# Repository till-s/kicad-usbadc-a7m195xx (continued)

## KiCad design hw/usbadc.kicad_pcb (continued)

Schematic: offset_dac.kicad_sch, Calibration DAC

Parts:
C98, C105, C107, C108, C109, C147, C148: 100n; C_0603_1608Metric; Part CL10B104KB8NFN
C99, C106, C112, C113: 1u; C_0805_2012Metric; Part CGA4J2X7R1C105K125AA
Q1, Q3: SSM6N35AFE; SOT-563-adjusted; Part SSM6N35AFE
R25, R35, R90, R91, R92, R93: 80k6; R_0603_1608Metric; Part RMCF0603FT80K6
R48, R49: 100k; R_0603_1608Metric; Part RMCF0603FT100K
R61, R62, R71, R79, R87, R89: 18k; R_0603_1608Metric; Part RMCF0603FT18K0
R80, R81, R82, R85: 1k; R_0603_1608Metric; Part RMCF0603FT1K00
R86, R88: 59k0; R_0603_1608Metric; Part RMCF0603FT59K0
R94, R95: 1; R_0603_1608Metric; Part RMCF0603FT1R00
U22: TSV992A; DFN-8-1EP_2x2mm_P0.5mm_EP0.45x1.6mm; Part TSV992IQ2
U23: MCP47CVB12-E_UN; MSOP-10_3x3mm_P0.5mm; Part MCP47CVB12-E/UN

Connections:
+2V5_analog: C105.1, C106.1, C107.2, U22.8 (V+), U23.1 (VDD), U23.2 (A0); also elsewhere on the board
-2V5_analog: C98.1, C99.1, U22.4 (V-); also elsewhere on the board
/Front End/FE_CHA/PGA_INLO: C113.1, R93.1, R95.1; also elsewhere on the board
/Front End/FE_CHB/PGA_INLO: C112.1, R92.1, R94.1; also elsewhere on the board
/Front End/fe_ctl/P0: Q1.2 (G), Q1.5 (G), R48.2; also elsewhere on the board
/Front End/fe_ctl/P1: Q3.2 (G), Q3.5 (G), R49.2; also elsewhere on the board
/I2C_SCL_2V5: U23.9 (SCL); also elsewhere on the board
/I2C_SDA_2V5: U23.10 (SDA); also elsewhere on the board
GND: C98.2, C99.2, C105.2, C106.2, C107.1, C112.2, C113.2, C147.2, C148.2, Q1.1 (S), Q1.4 (S), Q3.1 (S), Q3.4 (S), R25.1, R35.1, R48.1, R49.1, R90.2, R91.2, U23.6 (LATn), U23.7 (VSS), U23.8 (A1); also elsewhere on the board
unnamed: C108.1, R94.2, U22.1
unnamed: C109.1, R95.2, U22.7
unnamed: Q1.6 (D), R80.1
unnamed: Q1.3 (D), R81.1
unnamed: Q3.6 (D), R82.1
unnamed: Q3.3 (D), R85.1
unnamed: R61.2, R80.2, R86.1
unnamed: R62.2, R81.2, R87.1
unnamed: R71.2, R82.2, R88.1
unnamed: R79.2, R85.2, R89.1
unnamed: C148.1, R25.2, R86.2, R90.1, U22.3 (+)
unnamed: C108.2, R87.2, R92.2, U22.2 (-)
unnamed: C147.1, R35.2, R88.2, R91.1, U22.5 (+)
unnamed: C109.2, R89.2, R93.2, U22.6 (-)
unnamed: R79.1, U23.4 (VOUT0)
unnamed: R62.1, U23.5 (VOUT1)
unnamed: R61.1, R71.1, U23.3 (VREF)

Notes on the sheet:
I2C Address 0x61 MCP47CVB02: 8-bit MCP47CVB12: 10-bit MCP47CVB22: 12-bit

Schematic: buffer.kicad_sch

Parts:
C2001, C2002, C2003, C2006, C2008, C2010, C2012, C2014, C2016, C2017: 100n; C_0603_1608Metric; Part CL10B104KB8NFN
C2004: 10p; C_0402_1005Metric
C2005: 10n; C_0805_2012Metric
C2007, C2013, C2015: 2n; C_0603_1608Metric
C2009, C2011: 1u; C_0805_2012Metric; Part CGA4J2X7R1C105K125AA
D2001: NSR0170HT1G; D_SOD-323; Part NSR0170HT1G
J2001: BNC; BNC_Molex_0731713150; Part 0731713150
J2002: RFShield_Front; Leader SMS-255F; Part SMS-255F+C
J2003: RFShield_Back; SMS-202F; Part SMS-202F+C
JP2001: 50Ohm; J_0603_V
K2001: G6L-1F; Part G6L-1F
R2001, R2003, R2008: 1M; R_0603_1608Metric
R2002: 1k; R_0603_1608Metric
R2004: 1M; R_0402_1005Metric
R2005: 100k/100p; RC_0603_1608Metric
R2006, R2007: 909k/11p; RC_0603_1608Metric
U2001: TS5A63157DCK; SOT-363_SC-70-6_small_cyd
U2002: AQY280S; SOP-4_3.8x4.1mm_P2.54mm
U2003: AD8370; TSSOP-16-1EP_4.4x5mm_P0.65mm_EP3x3mm_ThermalVias
U2004: OPA859xDSG; WSON-8-1EP_2x2mm_P0.5mm_EP0.9x1.6mm

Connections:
+2V5_analog: C2010.1, C2011.1, C2014.1, C2015.1, C2016.1, C2017.1, U2003.3 (VCCI), U2003.4 (PWUP), U2003.6 (VCCO), U2003.11 (VCCO), U2004.7 (V+), U2004.8 (~PD); also elsewhere on the board
-2V5_analog: C2008.1, C2009.1, C2012.1, C2013.1, C2016.2, C2017.2, R2008.1, U2003.2 (ICOM), U2003.7 (OCOM), U2003.10 (OCOM), U2003.15 (ICOM), U2003.17 (ICOM), U2004.5 (V-); also elsewhere on the board
/ADC/ADC_CHB_IN_N: U2003.8 (OPHI); also elsewhere on the board
/ADC/ADC_CHB_IN_P: U2003.9 (OPLO); also elsewhere on the board
/Front End/FE_CHA/PGA_CTL_CLK: U2003.13 (CLCK); also elsewhere on the board
/Front End/FE_CHA/PGA_CTL_DATA: U2003.14 (DATA); also elsewhere on the board
/Front End/FE_CHB/FE_CTL_AC: R2002.2; also elsewhere on the board
/Front End/FE_CHB/FE_CTL_ATT: R2001.2, R2003.2; also elsewhere on the board
/Front End/FE_CHB/FE_CTL_TERM: D2001.1 (K), K2001.5; also elsewhere on the board
/Front End/FE_CHB/PGA_CTL_LATCH: U2003.12 (LTCH); also elsewhere on the board
/Front End/FE_CHB/PGA_INLO: C2003.1, U2003.16 (INLO); also elsewhere on the board
GND: C2001.2, C2002.1, C2003.2, C2006.1, C2007.2, C2008.2, C2009.2, C2010.2, C2011.2, C2012.2, C2013.2, C2014.2, C2015.2, D2001.2 (A), J2001.2 (Ext), J2002.1 (Shield), J2003.1 (Shield), K2001.2, K2001.8, R2003.1, U2001.2 (GND), U2001.3 (NC), U2002.2, U2004.4 (+); also elsewhere on the board
unnamed: C2005.2, J2001.1 (In), JP2001.1 (A), U2002.4
unnamed: C2005.1, JP2001.3 (B), R2006.2, U2002.3
unnamed: JP2001.2 (C), K2001.4
unnamed: R2002.1, U2002.1
unnamed: R2005.2, R2006.1, R2007.2
unnamed: R2005.1, U2001.4 (COM)
unnamed: C2001.1, R2001.1, U2001.6 (IN)
unnamed: C2004.1, R2004.2, R2007.1, U2001.1 (NO), U2004.3 (-)
unnamed: U2003.1 (INHI), U2004.6
unnamed: C2007.1, U2003.5 (VOCM)
unnamed: C2006.2, R2008.2, U2004.9 (EP)
unnamed: C2004.2, R2004.1, U2004.1 (FB)
Vpp_analog: C2002.2, U2001.5 (V+); also elsewhere on the board

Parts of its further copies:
C1001, C1002, C1003, C1006, C1008, C1010, C1012, C1014, C1016, C1017: 100n; C_0603_1608Metric; Part CL10B104KB8NFN
C1004: 10p; C_0402_1005Metric
C1005: 10n; C_0805_2012Metric
C1007, C1013, C1015: 2n; C_0603_1608Metric
C1009, C1011: 1u; C_0805_2012Metric; Part CGA4J2X7R1C105K125AA
D1001: NSR0170HT1G; D_SOD-323; Part NSR0170HT1G
J1001: BNC; BNC_Molex_0731713150; Part 0731713150
J1002: RFShield_Front; Leader SMS-255F; Part SMS-255F+C
J1003: RFShield_Back; SMS-202F; Part SMS-202F+C
JP1001: 50Ohm; J_0603_V
K1001: G6L-1F; Part G6L-1F
R1001, R1003, R1008: 1M; R_0603_1608Metric
R1002: 1k; R_0603_1608Metric
R1004: 1M; R_0402_1005Metric
R1005: 100k/100p; RC_0603_1608Metric
R1006, R1007: 909k/11p; RC_0603_1608Metric
U1001: TS5A63157DCK; SOT-363_SC-70-6_small_cyd
U1002: AQY280S; SOP-4_3.8x4.1mm_P2.54mm
U1003: AD8370; TSSOP-16-1EP_4.4x5mm_P0.65mm_EP3x3mm_ThermalVias
U1004: OPA859xDSG; WSON-8-1EP_2x2mm_P0.5mm_EP0.9x1.6mm

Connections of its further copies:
+2V5_analog: C1010.1, C1011.1, C1014.1, C1015.1, C1016.1, C1017.1, U1003.3 (VCCI), U1003.4 (PWUP), U1003.6 (VCCO), U1003.11 (VCCO), U1004.7 (V+), U1004.8 (~PD); also elsewhere on the board
-2V5_analog: C1008.1, C1009.1, C1012.1, C1013.1, C1016.2, C1017.2, R1008.1, U1003.2 (ICOM), U1003.7 (OCOM), U1003.10 (OCOM), U1003.15 (ICOM), U1003.17 (ICOM), U1004.5 (V-); also elsewhere on the board
/ADC/ADC_CHA_IN_N: U1003.8 (OPHI); also elsewhere on the board
/ADC/ADC_CHA_IN_P: U1003.9 (OPLO); also elsewhere on the board
/Front End/FE_CHA/FE_CTL_AC: R1002.2; also elsewhere on the board
/Front End/FE_CHA/FE_CTL_ATT: R1001.2, R1003.2; also elsewhere on the board
/Front End/FE_CHA/FE_CTL_TERM: D1001.1 (K), K1001.5; also elsewhere on the board
/Front End/FE_CHA/PGA_CTL_CLK: U1003.13 (CLCK); also elsewhere on the board
/Front End/FE_CHA/PGA_CTL_DATA: U1003.14 (DATA); also elsewhere on the board
/Front End/FE_CHA/PGA_CTL_LATCH: U1003.12 (LTCH); also elsewhere on the board
/Front End/FE_CHA/PGA_INLO: C1003.1, U1003.16 (INLO); also elsewhere on the board
GND: C1001.2, C1002.1, C1003.2, C1006.1, C1007.2, C1008.2, C1009.2, C1010.2, C1011.2, C1012.2, C1013.2, C1014.2, C1015.2, D1001.2 (A), J1001.2 (Ext), J1002.1 (Shield), J1003.1 (Shield), K1001.2, K1001.8, R1003.1, U1001.2 (GND), U1001.3 (NC), U1002.2, U1004.4 (+); also elsewhere on the board
unnamed: C1005.2, J1001.1 (In), JP1001.1 (A), U1002.4
unnamed: C1005.1, JP1001.3 (B), R1006.2, U1002.3
unnamed: JP1001.2 (C), K1001.4
unnamed: R1002.1, U1002.1
unnamed: R1005.2, R1006.1, R1007.2
unnamed: R1005.1, U1001.4 (COM)
unnamed: C1001.1, R1001.1, U1001.6 (IN)
unnamed: C1004.1, R1004.2, R1007.1, U1001.1 (NO), U1004.3 (-)
unnamed: U1003.1 (INHI), U1004.6
unnamed: C1007.1, U1003.5 (VOCM)
unnamed: C1006.2, R1008.2, U1004.9 (EP)
unnamed: C1004.2, R1004.1, U1004.1 (FB)
Vpp_analog: C1002.2, U1001.5 (V+); also elsewhere on the board

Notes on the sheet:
Ideally: 101k//99p but 99p is not available
Populate 1-2 or 2-3 with 50Ohm termination resistor depending on whether you like the termination to be AC- or DC-coupled.

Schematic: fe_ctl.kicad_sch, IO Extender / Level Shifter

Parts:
C9, C140: 100n; C_0603_1608Metric; Part CL10B104KB8NFN
R60: 10k; R_0603_1608Metric; Part RMCF0603FT10K0
U21: TCA6408A; QFN-16-1EP_3x3mm_P0.5mm_EP1.45x1.45mm_ThermalVias; Part TCA6408ARGTR

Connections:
+3V3: C140.1, R60.2, U21.15 (VCCi); also elsewhere on the board
+4V: C9.1, U21.14 (VCCp); also elsewhere on the board
/Front End/FE_CHA/FE_CTL_AC: U21.8 (P5); also elsewhere on the board
/Front End/FE_CHA/FE_CTL_ATT: U21.7 (P4); also elsewhere on the board
/Front End/FE_CHB/FE_CTL_AC: U21.5 (P3); also elsewhere on the board
/Front End/FE_CHB/FE_CTL_ATT: U21.4 (P2); also elsewhere on the board
/Front End/fe_ctl/P0: U21.2 (P0); also elsewhere on the board
/Front End/fe_ctl/P1: U21.3 (P1); also elsewhere on the board
/Front End/fe_ctl/P6: U21.9 (P6); also elsewhere on the board
/Front End/fe_ctl/P7: U21.10 (P7); also elsewhere on the board
GND: C9.2, C140.2, U21.6 (GND), U21.16 (ADDR); also elsewhere on the board
I2C_SCL_3V3: U21.12 (SCL); also elsewhere on the board
I2C_SDA_3V3: U21.13 (SDA); also elsewhere on the board
unnamed: R60.1, U21.1 (RESETb)

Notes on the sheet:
NOTES: I2C Address 0x40 ADDR: VCCp levels RESETb: VCCi levels PAD: seems unconnected

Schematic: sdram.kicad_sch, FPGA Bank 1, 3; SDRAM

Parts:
C37, C39, C50, C51, C52, C53, C54, C55, C84, C86, C92, C93, C94: 100n; C_0603_1608Metric; Part CL10B104KB8NFN
C38, C72: 4u7; C_0805_2012Metric; Part 2012X5R1C475K125AC
FB4: 600Ohm@100MHz; L_0603_1608Metric; Part MI0603J601R-10
R83, R84, R100, R101, R102, R121: 10k; R_0603_1608Metric; Part RMCF0603FT10K0
R122: 10k; R_0603_1608Metric; Part RMCF0603FT10K0; not fitted
U15: T20Q144xx; LQFP-144_20x20mm_P0.5mm; Part T20Q144C4
U17: NDS36PT5-16ET; TSOP-II-54_22.2x10.16mm_P0.8mm; Part NDS36PT5-16ET

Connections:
+3V3: C37.1, C38.1, C39.1, C50.1, C51.1, C84.1, C86.1, C92.1, C93.1, C94.1, FB4.2, R83.1, R84.1, R100.1, R101.1, R102.1, R121.1, U15.12 (VCCIO1C_1D), U15.21 (VCCIO1B), U15.88 (VCCIO3E), U15.91 (VCCIO3D), U15.95 (VCCIO3B_3C), U15.143 (VCCIO1E), U17.1 (VDD), U17.14 (VDD), U17.27 (VDD); also elsewhere on the board
/FPGA Trion/sdram/A0: U15.144 (GPIOL_64), U17.23 (A0)
/FPGA Trion/sdram/A1: U15.138 (GPIOL_69_CBSEL1), U17.24 (A1)
/FPGA Trion/sdram/A2: U15.140 (GPIOL_67_CDI13), U17.25 (A2)
/FPGA Trion/sdram/A3: U15.141 (GPIOL_65), U17.26 (A3)
/FPGA Trion/sdram/A6: U15.106 (GPIOR_94_CDI27), U17.31 (A6)
/FPGA Trion/sdram/A7: U15.105 (GPIOR_95_CDI26), U17.32 (A7)
/FPGA Trion/sdram/A8: U15.103 (GPIOR_104_CDI25), U17.33 (A8)
/FPGA Trion/sdram/A9: U15.102 (GPIOR_105_CDI24), U17.34 (A9)
/FPGA Trion/sdram/A10: U15.142 (GPIOL_66_CDI12), U17.22 (A10)
/FPGA Trion/sdram/BA0: U15.4 (GPIOL_54_CDI11), U17.20 (BA0)
/FPGA Trion/sdram/BA1: U15.3 (GPIOL_53_CDI10), U17.21 (BA1)
/FPGA Trion/sdram/CASb: U15.8 (GPIOL_40_CDI8), U17.17 (~CAS)
/FPGA Trion/sdram/CLK: U15.98 (GPIOR_117_CTRL14), U17.38 (CLK)
/FPGA Trion/sdram/CSb: R83.2, U15.6 (GPIOL_46), U17.19 (~CS)
/FPGA Trion/sdram/DQ1: U15.20 (GPIOL_12_CDI2), U17.4 (DQ1)
/FPGA Trion/sdram/DQ2: U15.19 (GPIOL_13_CDI3), U17.5 (DQ2)
/FPGA Trion/sdram/DQ3: U15.18 (GPIOL_20_CTRL0_CDI4), U17.7 (DQ3)
/FPGA Trion/sdram/DQ4: U15.17 (GPIOL_21_CTRL1_CDI5), U17.8 (DQ4)
/FPGA Trion/sdram/DQ5: U15.16 (GPIOL_22_CTRL2), U17.10 (DQ5)
/FPGA Trion/sdram/DQ6: U15.15 (GPIOL_24_CLK0), U17.11 (DQ6)
/FPGA Trion/sdram/DQ7: U15.14 (GPIOL_25_CLK1), U17.13 (DQ7)
/FPGA Trion/sdram/DQ8: U15.100 (GPIOR_113_CDI22), U17.42 (DQ8)
/FPGA Trion/sdram/DQ9: U15.99 (GPIOR_116_CTRL15), U17.44 (DQ9)
/FPGA Trion/sdram/DQ10: U15.97 (GPIOR_122_CLK13_CDI21), U17.45 (DQ10)
/FPGA Trion/sdram/DQ11: U15.87 (GPIOR_132_CDI19), U17.47 (DQ11)
/FPGA Trion/sdram/DQ12: U15.86 (GPIOR_133_CDI18), U17.48 (DQ12)
/FPGA Trion/sdram/DQ13: U15.81 (GPIOR_139), U17.50 (DQ13)
/FPGA Trion/sdram/DQ14: U15.77 (GPIOR_154), U17.51 (DQ14)
/FPGA Trion/sdram/DQ15: R84.2, U15.74 (GPIOR_158_TEST_N), U17.53 (DQ15)
/FPGA Trion/sdram/DQMH: U15.101 (GPIOR_112_CDI23), U17.39 (DQMH)
/FPGA Trion/sdram/DQML: U15.11 (GPIOL_31_CLK7_CDI6), U17.15 (DQML)
/FPGA Trion/sdram/RASb: U15.7 (GPIOL_41_CDI9), U17.18 (~RAS)
/FPGA Trion/sdram/WEb: U15.10 (GPIOL_32_CTRL4_CDI7), U17.16 (~WE)
ADC_D0: U15.93 (GPIOR_123_CLK12_CDI20); also elsewhere on the board
ADC_D1: U15.92 (GPIOR_125_CLK10); also elsewhere on the board
ADC_D2: U15.90 (GPIOR_128_CTRL11); also elsewhere on the board
ADC_D3: U15.89 (GPIOR_129_CTRL10); also elsewhere on the board
ADC_D4: U15.84 (GPIOR_135_CDI17); also elsewhere on the board
ADC_D5: U15.83 (GPIOR_136_CDI16); also elsewhere on the board
ADC_D6: U15.82 (GPIOR_138); also elsewhere on the board
ADC_D7: R102.2, U15.80 (GPIOR_149_CBUS2); also elsewhere on the board
ADC_D8: R101.2, U15.79 (GPIOR_150_CBUS1); also elsewhere on the board
ADC_D9: R100.2, U15.78 (GPIOR_151_CBUS0); also elsewhere on the board
ADC_DCLK: U15.75 (GPIOR_157_PLLIN); also elsewhere on the board
ADC_DOR: U15.76 (GPIOR_155); also elsewhere on the board
ADC_SHDN: R121.2, R122.1; also elsewhere on the board
GND: C37.2, C38.2, C39.2, C50.2, C51.2, C52.2, C53.2, C54.2, C55.2, C72.2, C84.2, C86.2, C92.2, C93.2, C94.2, R122.2, U17.6 (VSSQ), U17.12 (VSSQ), U17.28 (VSS), U17.41 (VSS), U17.46 (VSSQ), U17.52 (VSSQ), U17.54 (VSS); also elsewhere on the board
I2C_SCL_3V3: U15.134 (GPIOL_73_EXTFB1_CDI15); also elsewhere on the board
unnamed: C52.1, C53.1, C54.1, C55.1, C72.1, FB4.1, U17.3 (VDDQ), U17.9 (VDDQ), U17.43 (VDDQ), U17.49 (VDDQ)
SDRAM_A4: U17.29 (A4); also elsewhere on the board
SDRAM_A5: U17.30 (A5); also elsewhere on the board
SDRAM_A11: U17.35 (A11); also elsewhere on the board
SDRAM_A12: U17.36 (A12); also elsewhere on the board
SDRAM_CKE: U15.139 (GPIOL_68), U17.37 (CKE)
SDRAM_DQ0: U17.2 (DQ0); also elsewhere on the board
ULPI_CLK: U15.132 (GPIOL_74_PLLIN0); also elsewhere on the board
ULPI_DIR: U15.135 (GPIOL_72_EXTFB0_CDI14); also elsewhere on the board
ULPI_NXT: U15.131 (GPIOL_75_PLLIN1); also elsewhere on the board
ULPI_RSTb_CLKSEL: U15.137 (GPIOL_70_CBSEL0); also elsewhere on the board
ULPI_STP: U15.136 (GPIOL_71_NSTATUS); also elsewhere on the board

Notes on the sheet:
Prevent ADC from driving ADC_D7..D9 by pulling up ADC_SHDN. Ensures the CBUS configuration pins are pulled up. Once configured the FPGA can drive ADC_SHDN low to activate.

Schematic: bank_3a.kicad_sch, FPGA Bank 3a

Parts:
C36: 100n; C_0603_1608Metric; Part CL10B104KB8NFN
U15: T20Q144xx; LQFP-144_20x20mm_P0.5mm; Part T20Q144C4

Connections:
+3V3: C36.1, U15.122 (VCCIO3A); also elsewhere on the board
FPGA_CLK: U15.124 (GPIOR_76_PLLIN0); also elsewhere on the board
GND: C36.2; also elsewhere on the board
SDRAM_A4: U15.110 (GPIOR_87_CDI29); also elsewhere on the board
SDRAM_A5: U15.109 (GPIOR_88_CDI28); also elsewhere on the board
SDRAM_A11: U15.112 (GPIOR_86); also elsewhere on the board
SDRAM_A12: U15.111 (GPIOR_85); also elsewhere on the board
ULPI_D0: U15.123 (GPIOR_77_PLLIN1); also elsewhere on the board
ULPI_D1: U15.119 (GPIOR_78_EXTFB0_CDI31); also elsewhere on the board
ULPI_D2: U15.118 (GPIOR_79_EXTFB1_CDI30); also elsewhere on the board
ULPI_D3: U15.117 (GPIOR_80); also elsewhere on the board
ULPI_D4: U15.116 (GPIOR_81_MREFCLK); also elsewhere on the board
ULPI_D5: U15.115 (GPIOR_82); also elsewhere on the board
ULPI_D6: U15.114 (GPIOR_83); also elsewhere on the board
ULPI_D7: U15.113 (GPIOR_84); also elsewhere on the board

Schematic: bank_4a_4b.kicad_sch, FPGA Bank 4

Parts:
C137, C138, C139: 100n; C_0603_1608Metric; Part CL10B104KB8NFN
U15: T20Q144xx; LQFP-144_20x20mm_P0.5mm; Part T20Q144C4

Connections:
+3V3: C137.1, C138.1, C139.1, U15.51 (VCCIO4B), U15.52 (VCCIO4B), U15.62 (VCCIO4A), U15.63 (VCCIO4A); also elsewhere on the board
ADC_CSb: U15.70 (GPIOB_RXP12_EXTFB0); also elsewhere on the board
ADC_SCLK: U15.71 (GPIOB_CLKP0); also elsewhere on the board
ADC_SDIO: U15.72 (GPIOB_CLKN0); also elsewhere on the board
ADC_SHDN: U15.53 (GPIOB_TXP11); also elsewhere on the board
ADC_SYNC: U15.66 (GPIOB_RXP07); also elsewhere on the board
EXP_IO1: U15.40 (GPIOB_TXP02); also elsewhere on the board
EXP_IO2: U15.38 (GPIOB_TXP00); also elsewhere on the board
GND: C137.2, C138.2, C139.2; also elsewhere on the board
GPIO_DAT: U15.42 (GPIOB_TXP04); also elsewhere on the board
GPIO_DIR: U15.43 (GPIOB_TXN04); also elsewhere on the board
I2C_SDA_3V3: U15.54 (GPIOB_TXN11); also elsewhere on the board
LED_CHA_B: U15.55 (GPIOB_RXP00); also elsewhere on the board
LED_CHA_G: U15.59 (GPIOB_RXN02); also elsewhere on the board
LED_CHA_R: U15.60 (GPIOB_RXN03); also elsewhere on the board
LED_CHB_B: U15.56 (GPIOB_RXN00); also elsewhere on the board
LED_CHB_G: U15.61 (GPIOB_RXP03); also elsewhere on the board
LED_CHB_R: U15.58 (GPIOB_RXP02); also elsewhere on the board
LED_FL_B: U15.41 (GPIOB_TXN02); also elsewhere on the board
LED_FL_G: U15.39 (GPIOB_TXN00); also elsewhere on the board
LED_FR_B: U15.47 (GPIOB_TXP09); also elsewhere on the board
LED_FR_G: U15.45 (GPIOB_TXP06); also elsewhere on the board
LED_FR_R: U15.48 (GPIOB_TXN09); also elsewhere on the board
LED_FR_S: U15.46 (GPIOB_TXN06); also elsewhere on the board
PGA_LATCH_CHA: U15.68 (GPIOB_RXN10); also elsewhere on the board
PGA_LATCH_CHB: U15.67 (GPIOB_RXP10); also elsewhere on the board
PGA_SCLK: U15.69 (GPIOB_RXN12_EXTFB0); also elsewhere on the board
PGA_SDAT: U15.65 (GPIOB_RXN07); also elsewhere on the board

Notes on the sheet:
The filename is 'unused' for legacy reasons.
REF_RES is not a GPIO

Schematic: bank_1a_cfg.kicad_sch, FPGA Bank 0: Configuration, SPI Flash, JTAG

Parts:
C95, C96, C118, C120, C122, C124, C125, C126, C127, C128, C129, C130, C131, C132: 100n; C_0603_1608Metric; Part CL10B104KB8NFN
C103, C104, C114, C133, C134, C135: 1u; C_0805_2012Metric; Part CGA4J2X7R1C105K125AA
C117, C136: 10u; C_1206_3216Metric; Part CL31A106KPHNNNE
C119, C121, C123: 4u7; C_0805_2012Metric; Part 2012X5R1C475K125AC
D4: NSR0170HT1G; D_SOD-323; Part NSR0170HT1G
FB6, FB7, FB8: 600Ohm@100MHz; L_0603_1608Metric; Part MI0603J601R-10
J4: T8_JTAG; PinHeader_2x07_P2.00mm_Vertical; Part 2PH2-14-UA
R50, R103, R104, R105, R106, R107, R108, R109, R110, R111, R112, R113, R119, R120: 10k; R_0603_1608Metric; Part RMCF0603FT10K0
R52: 10k; R_0603_1608Metric; Part RMCF0603FT10K0; not fitted
R125: 1k; R_0603_1608Metric; Part RMCF0603FT1K00
SW1: Reconfig; SW_SPST_PTS810_and_PTS841; Part PTS841GKSMTR
U15: T20Q144xx; LQFP-144_20x20mm_P0.5mm; Part T20Q144C4
U24: AT25FF081A-SSHN-B; SOIC-8_3.9x4.9mm_P1.27mm; Part AT25FF081A-SSHN-B
U26: TLV803EA29DBZR; SOT-23; Part TLV803EA29DBZR

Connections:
+1V2: C124.1, C125.1, C126.1, C127.1, C128.1, C129.1, C130.1, C131.1, C132.1, C133.1, C134.1, C135.1, C136.1, FB6.1, FB7.1, FB8.1, U15.13 (VCC), U15.22 (VCC), U15.49 (VCC), U15.57 (VCC), U15.85 (VCC), U15.96 (VCC), U15.125 (VCC), U15.128 (VCC), U15.130 (VCC); also elsewhere on the board
+3V3: C95.1, C96.1, C103.1, C104.1, C114.1, C117.1, R103.1, R104.1, R105.1, R106.1, R107.1, R108.1, R109.1, R110.1, R111.1, R112.1, R113.1, R119.1, U15.23 (VCCIO1A), U24.8 (VCC); also elsewhere on the board
/FPGA Trion/CDON: R111.2, U15.34 (CDONE); also elsewhere on the board
/FPGA Trion/bank_1a_cfg/CRESET_N: J4.3, R110.2, R125.2, U15.35 (CRESET_N)
/PWR_GOOD: D4.1 (K); also elsewhere on the board
GND: C95.2, C96.2, C103.2, C104.2, C114.2, C117.2, C118.2, C119.2, C120.2, C121.2, C122.2, C123.2, C124.2, C125.2, C126.2, C127.2, C128.2, C129.2, C130.2, C131.2, C132.2, C133.2, C134.2, C135.2, C136.2, J4.2, J4.4, J4.6, J4.8, J4.10, J4.12, R50.1, R52.1, SW1.1, SW1.3 (Shield), U15.1 (GND), U15.5 (GND), U15.9 (GND), U15.37 (GND), U15.44 (GND), U15.50 (GND), U15.64 (GND), U15.94 (GND), U15.104 (GND), U15.108 (GND), U15.120 (GND), U15.121 (GND), U15.126 (GND), U15.127 (GND), U15.129 (GND), U15.133 (GND), U24.4 (GND), U26.1 (GND); also elsewhere on the board
LED_FL_R: R104.2, U15.32 (GPIOL_04_CSI); also elsewhere on the board
unnamed: D4.2 (A), R120.2, SW1.2
unnamed: J4.5, R107.2, U15.27 (TDI)
unnamed: J4.7, R108.2, U15.24 (TDO)
unnamed: J4.9, R106.2, U15.26 (TCK)
unnamed: J4.11, R109.2, U15.25 (TMS)
unnamed: J4.13, R105.2
unnamed: R103.2, U15.31 (GPIOL_00_SS_N), U24.1 (~CS)
unnamed: U15.30 (GPIOL_01_CCK), U24.6 (SCK)
unnamed: R50.2, U15.29 (GPIOL_08_CDI0), U24.5 (SI/IO0)
unnamed: R52.2, U15.28 (GPIOL_09_CDI1), U24.2 (SO/IO1)
unnamed: C118.1, C119.1, FB6.2, U15.73 (VCCA_BR)
unnamed: C120.1, C121.1, FB7.2, U15.2 (VCCA_TL)
unnamed: C122.1, C123.1, FB8.2, U15.107 (VCCA_TR)
unnamed: R112.2, U24.7 (~HOLD/IO3)
unnamed: R113.2, U24.3 (~WP/IO2)
unnamed: R125.1, U26.2 (RESET)
unnamed: R119.2, R120.1, U26.3 (V_{DD})
SDRAM_DQ0: U15.33 (GPIOL_05_CSO); also elsewhere on the board

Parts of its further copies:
C1001, C1002, C1008, C1010, C1012, C1014, C1016, C1017: 100n; C_0603_1608Metric; Part CL10B104KB8NFN

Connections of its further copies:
+2V5_analog: C1010.1, C1014.1, C1016.1, C1017.1; also elsewhere on the board
-2V5_analog: C1008.1, C1012.1, C1016.2, C1017.2; also elsewhere on the board
GND: C1001.2, C1002.1, C1008.2, C1010.2, C1012.2, C1014.2; also elsewhere on the board
unnamed 220: C1001.1; also elsewhere on the board
Vpp_analog: C1002.2; also elsewhere on the board

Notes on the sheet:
Note: the RDBZR parts use a different pinout!
JTAG Interface
Board version 3.2 did not populate R50 nor R52; can be used to distinguish board versions. 3.3 populates R50 only.

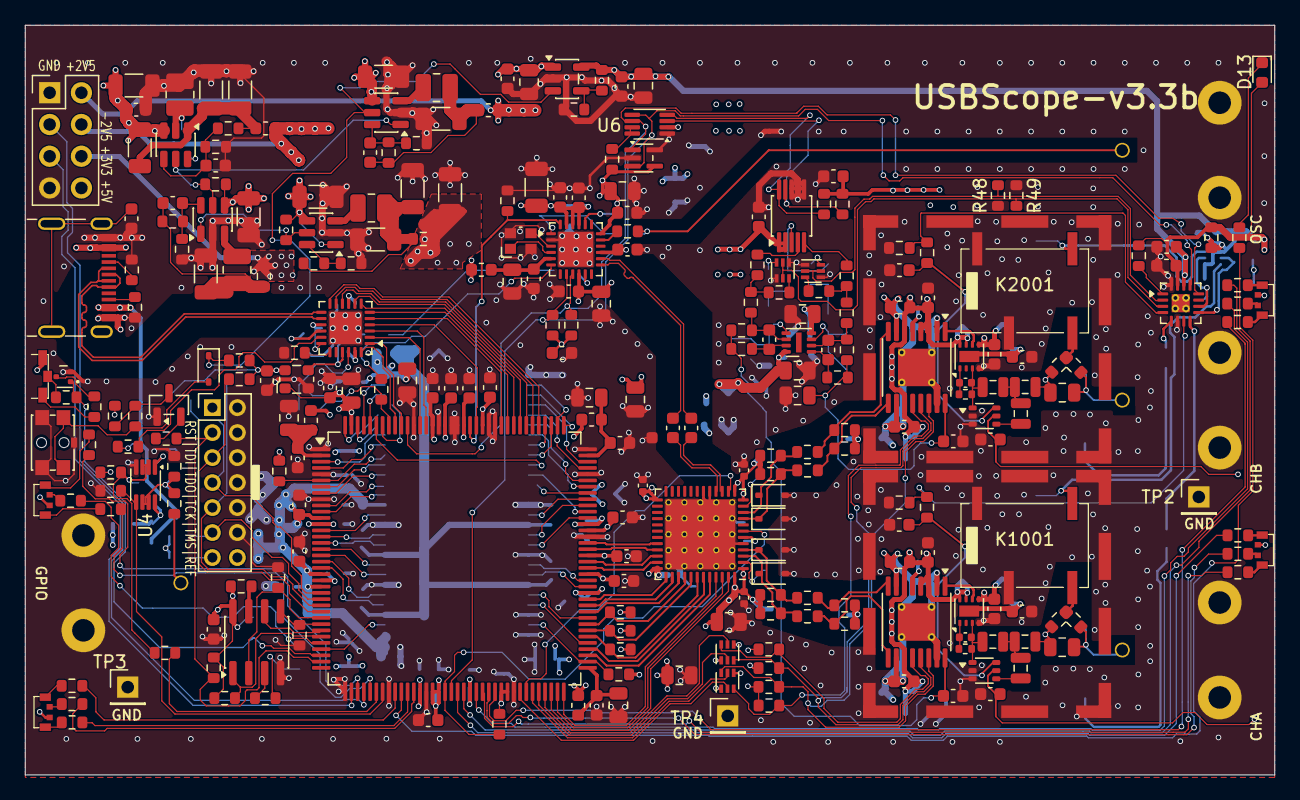
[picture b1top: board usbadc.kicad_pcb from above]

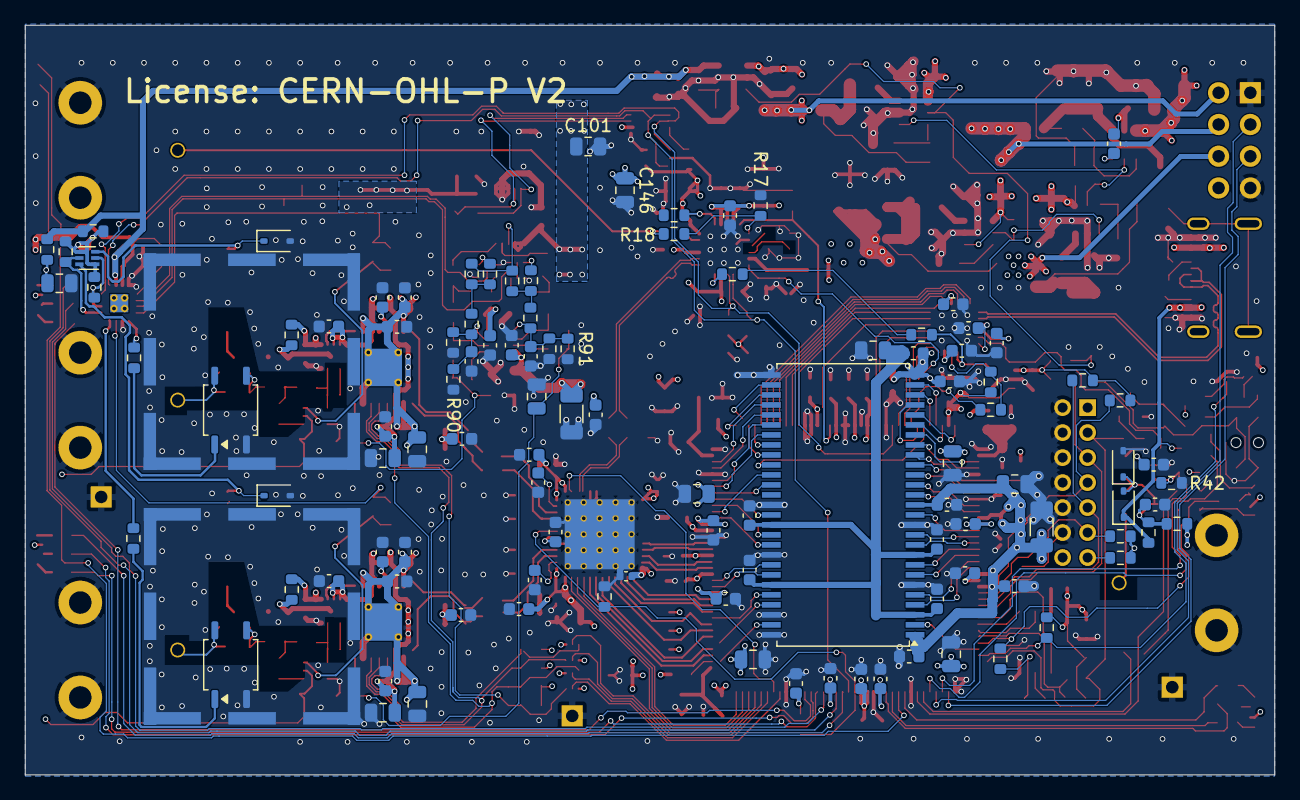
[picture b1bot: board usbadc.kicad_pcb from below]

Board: 4 copper layers, 100.0 x 60.0 mm, 373 parts (109 on the bottom side), 256 nets.

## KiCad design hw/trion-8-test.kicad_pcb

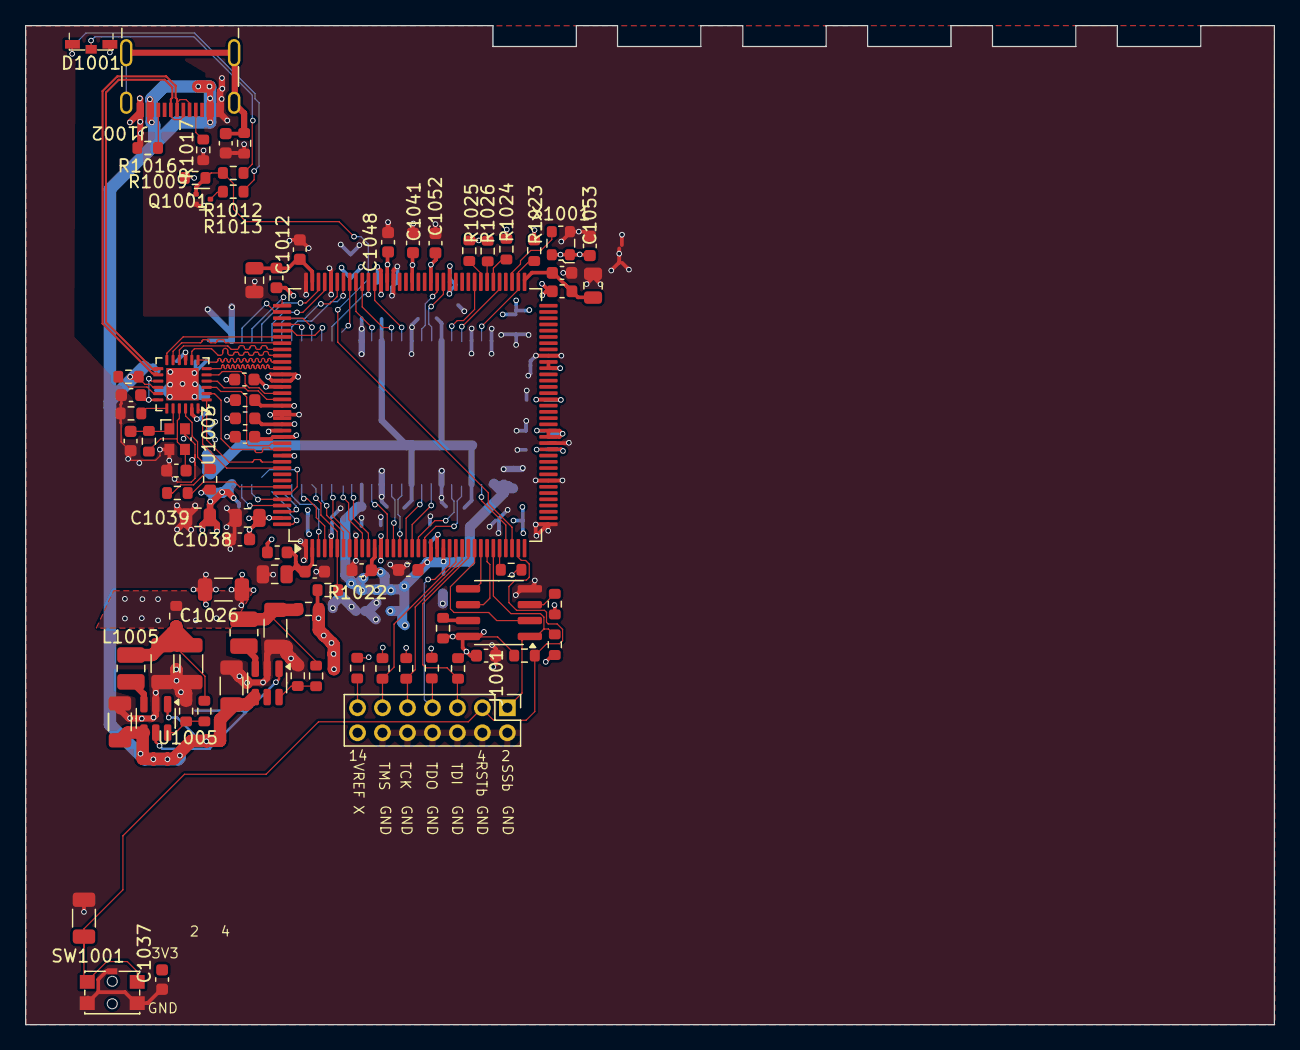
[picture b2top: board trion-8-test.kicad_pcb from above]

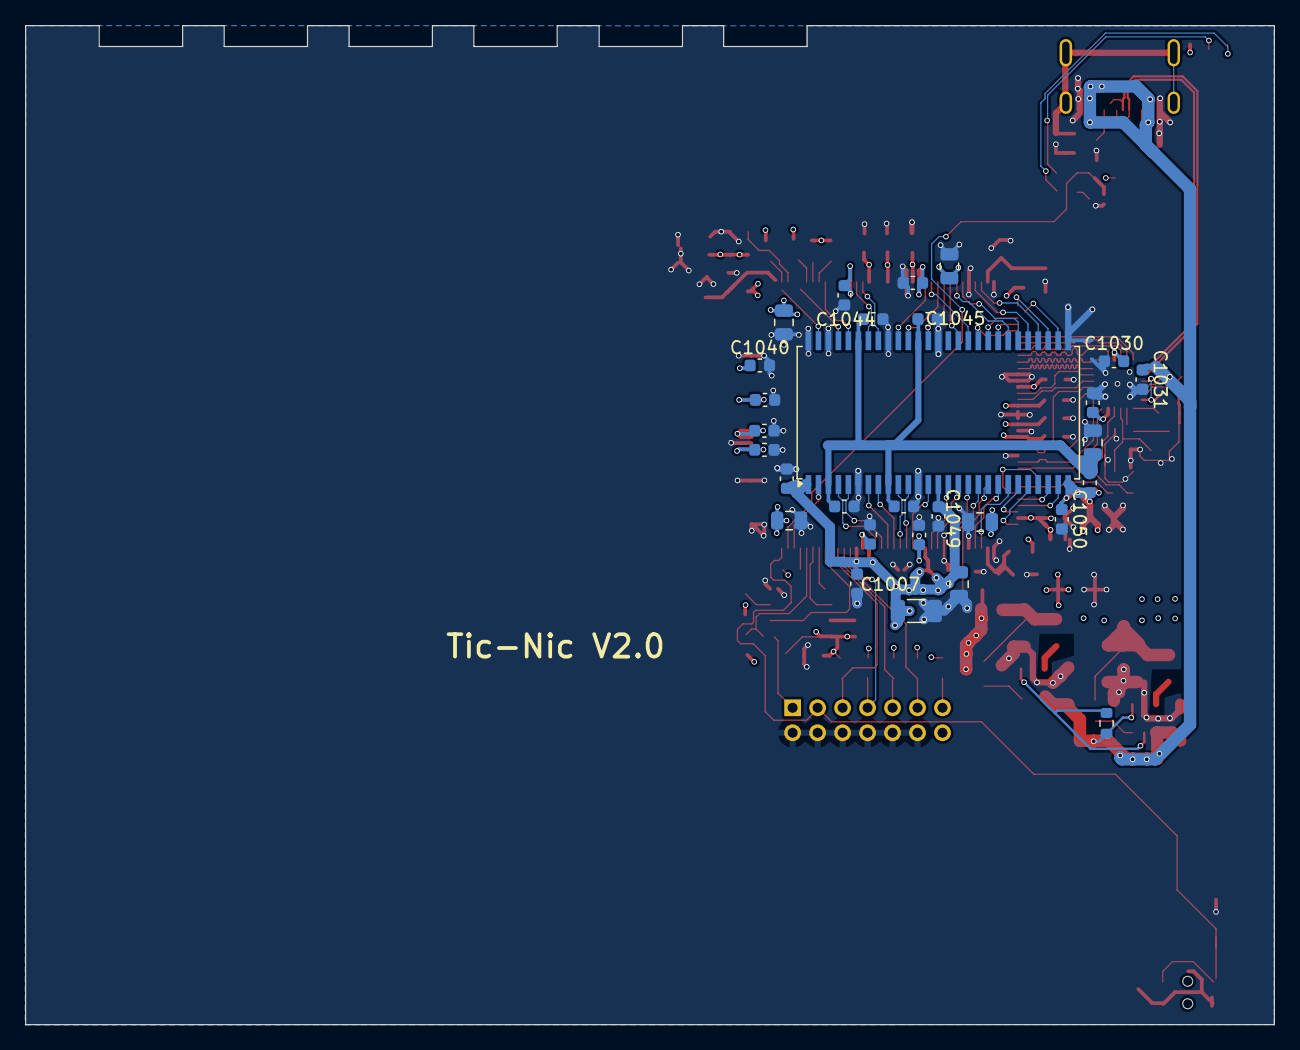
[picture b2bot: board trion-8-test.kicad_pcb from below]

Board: 4 copper layers, 100.0 x 80.0 mm, 110 parts (29 on the bottom side), 97 nets.

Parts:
C1001, C1002, C1008, C1010, C1012, C1014, C1015, C1016, C1017, C1018, C1019, C1020, C1021, C1022, C1027, C1030, C1031, C1035, C1036, C1037, C1038, C1040, C1041, C1042, C1043, C1044, C1045, C1046, C1048, C1049, C1050, C1051, C1052, C1053: 100n; C_0603_1608Metric
C1003, C1007, C1026, C1054, C1055, C1056, C1057, C1058: 10u; C_1206_3216Metric
C1004, C1005, C1006, C1023, C1024, C1025: 1u; C_0805_2012Metric
C1009, C1011, C1013, C1039, C1047: 4u7; C_0805_2012Metric
C1028, C1029: 1u; C_0603_1608Metric
C1032: 10n; C_0603_1608Metric
C1033, C1034: 10p; C_0603_1608Metric
D1001: LED_Dual_RAG; LED_Wuerth_Sideview
J1001: T8_JTAG; PinHeader_2x07_P2.00mm_Vertical
J1002: USB_C_Receptacle_USB2.0; USB_C_Receptacle_Molex_2171790001_16P_TopMnt_Horizontal
L1001, L1002, L1003, L1004: 600Ohm@100MHz; L_0603_1608Metric
L1005, L1006: 1u5; L_1008_2520Metric
Q1001: SSM3K37MFV; SOT-723
R1001, R1002, R1003, R1004, R1005, R1006, R1007, R1009, R1010, R1011, R1014, R1018, R1022, R1023, R1024, R1025, R1026, R1028, R1029, R1033: 10k; R_0603_1608Metric
R1008, R1030: 100k; R_0603_1608Metric
R1012, R1013: 1k; R_0603_1608Metric
R1015, R1027, R1031: 0; R_0603_1608Metric
R1016, R1017: 5k1; R_0603_1608Metric
R1019, R1020: 1M; R_0603_1608Metric
R1021: 8k06; R_0603_1608Metric
R1032: 45k3; R_0603_1608Metric
SW1001: Reconfig; SW_SPST_PTS810_and_PTS841
U1001: AT25FF081A-SSHN-B; SOIC-8_3.9x4.9mm_P1.27mm
U1002: T20Q144xx; LQFP-144_20x20mm_P0.5mm
U1003: USB3343; QFN-24-1EP_4x4mm_P0.5mm_EP2.6x2.6mm
U1004: NDS36PT5-16ET; TSOP-II-54_22.2x10.16mm_P0.8mm
U1005, U1006: RT8096B; SOT-23-6
X1001: ECS-2520MV-250-CM; Oscillator_SMD_ECS_2520MV-xxx-xx-4Pin_2.5x2.0mm
Y1001: 26MHz; Crystal_SMD_Abracon_ABM10-4Pin_2.5x2.0mm

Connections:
+1V2: C1014.1, C1015.1, C1016.1, C1017.1, C1018.1, C1019.1, C1020.1, C1021.1, C1022.1, C1023.1, C1024.1, C1025.1, C1026.1, L1001.1, L1002.1, L1003.1, R1027.2, U1002.13 (VCC), U1002.22 (VCC), U1002.49 (VCC), U1002.57 (VCC), U1002.85 (VCC), U1002.96 (VCC), U1002.125 (VCC), U1002.128 (VCC), U1002.130 (VCC)
+3V3: C1001.1, C1002.1, C1004.1, C1005.1, C1006.1, C1007.1, C1027.1, C1030.2, C1035.1, C1036.1, C1037.1, C1038.1, C1039.1, C1040.1, C1041.1, C1042.1, C1048.1, C1049.1, C1050.1, C1051.1, C1052.1, C1053.1, D1001.2 (A), L1004.2, R1001.1, R1002.1, R1003.1, R1004.1, R1005.1, R1006.1, R1007.1, R1008.1, R1009.1, R1010.1, R1011.1, R1014.1, R1022.1, R1023.1, R1024.1, R1025.1, R1026.1, R1031.2, U1001.8 (VCC), U1002.12 (VCCIO1C_1D), U1002.21 (VCCIO1B), U1002.23 (VCCIO1A), U1002.51 (VCCIO4B), U1002.52 (VCCIO4B), U1002.62 (VCCIO4A), U1002.63 (VCCIO4A), U1002.88 (VCCIO3E), U1002.91 (VCCIO3D), U1002.95 (VCCIO3B_3C), U1002.122 (VCCIO3A), U1002.143 (VCCIO1E), U1003.9 (VDDIO), U1004.1 (VDD), U1004.14 (VDD), U1004.27 (VDD), X1001.1 (Tri-State), X1001.4 (VDD)
+5V: C1031.1, C1054.1, C1057.1, J1002.A4 (VBUS), J1002.A9 (VBUS), J1002.B4 (VBUS), J1002.B9 (VBUS), R1018.1, R1030.1, U1003.16 (VBAT), U1005.1 (EN), U1005.4 (VIN), U1006.4 (VIN)
/sdram/A0: U1002.144 (GPIOL_64), U1004.23 (A0)
/sdram/A1: U1002.139 (GPIOL_68), U1004.24 (A1)
/sdram/A2: U1002.140 (GPIOL_67_CDI13), U1004.25 (A2)
/sdram/A3: U1002.141 (GPIOL_65), U1004.26 (A3)
/sdram/A6: U1002.106 (GPIOR_94_CDI27), U1004.31 (A6)
/sdram/A7: U1002.105 (GPIOR_95_CDI26), U1004.32 (A7)
/sdram/A8: U1002.103 (GPIOR_104_CDI25), U1004.33 (A8)
/sdram/A9: U1002.102 (GPIOR_105_CDI24), U1004.34 (A9)
/sdram/A10: U1002.142 (GPIOL_66_CDI12), U1004.22 (A10)
/sdram/BA0: U1002.4 (GPIOL_54_CDI11), U1004.20 (BA0)
/sdram/BA1: U1002.3 (GPIOL_53_CDI10), U1004.21 (BA1)
/sdram/CASb: U1002.8 (GPIOL_40_CDI8), U1004.17 (~CAS)
/sdram/CLK: U1002.98 (GPIOR_117_CTRL14), U1004.38 (CLK)
/sdram/CSb: R1022.2, U1002.6 (GPIOL_46), U1004.19 (~CS)
/sdram/DQ1: U1002.20 (GPIOL_12_CDI2), U1004.4 (DQ1)
/sdram/DQ2: U1002.19 (GPIOL_13_CDI3), U1004.5 (DQ2)
/sdram/DQ3: U1002.18 (GPIOL_20_CTRL0_CDI4), U1004.7 (DQ3)
/sdram/DQ4: U1002.17 (GPIOL_21_CTRL1_CDI5), U1004.8 (DQ4)
/sdram/DQ5: U1002.16 (GPIOL_22_CTRL2), U1004.10 (DQ5)
/sdram/DQ6: U1002.15 (GPIOL_24_CLK0), U1004.11 (DQ6)
/sdram/DQ7: U1002.14 (GPIOL_25_CLK1), U1004.13 (DQ7)
/sdram/DQ8: U1002.100 (GPIOR_113_CDI22), U1004.42 (DQ8)
/sdram/DQ9: U1002.99 (GPIOR_116_CTRL15), U1004.44 (DQ9)
/sdram/DQ10: U1002.97 (GPIOR_122_CLK13_CDI21), U1004.45 (DQ10)
/sdram/DQ11: U1002.87 (GPIOR_132_CDI19), U1004.47 (DQ11)
/sdram/DQ12: U1002.86 (GPIOR_133_CDI18), U1004.48 (DQ12)
/sdram/DQ13: U1002.81 (GPIOR_139), U1004.50 (DQ13)
/sdram/DQ14: U1002.77 (GPIOR_154), U1004.51 (DQ14)
/sdram/DQ15: R1023.2, U1002.74 (GPIOR_158_TEST_N), U1004.53 (DQ15)
/sdram/DQMH: U1002.101 (GPIOR_112_CDI23), U1004.39 (DQMH)
/sdram/DQML: U1002.11 (GPIOL_31_CLK7_CDI6), U1004.15 (DQML)
/sdram/RASb: U1002.7 (GPIOL_41_CDI9), U1004.18 (~RAS)
/sdram/WEb: U1002.10 (GPIOL_32_CTRL4_CDI7), U1004.16 (~WE)
/ulpi/ULPI_D0: U1002.124 (GPIOR_76_PLLIN0), U1003.4 (DATA0)
/ulpi/ULPI_D1: U1002.123 (GPIOR_77_PLLIN1), U1003.5 (DATA1)
/ulpi/ULPI_D2: U1002.119 (GPIOR_78_EXTFB0_CDI31), U1003.6 (DATA2)
/ulpi/ULPI_D3: U1002.118 (GPIOR_79_EXTFB1_CDI30), U1003.7 (DATA3)
/ulpi/ULPI_D4: U1002.117 (GPIOR_80), U1003.8 (DATA4)
/ulpi/ULPI_D5: U1002.116 (GPIOR_81_MREFCLK), U1003.10 (DATA5)
/ulpi/ULPI_D6: U1002.115 (GPIOR_82), U1003.11 (DATA6)
/ulpi/ULPI_D7: U1002.114 (GPIOR_83), U1003.12 (DATA7)
/ulpi/ULPI_USB_N: J1002.A7 (D-), J1002.B7 (D-), U1003.14 (DM)
/ulpi/ULPI_USB_P: J1002.A6 (D+), J1002.B6 (D+), U1003.13 (DP)
GND: C1001.2, C1002.2, C1003.2, C1004.2, C1005.2, C1006.2, C1007.2, C1008.2, C1009.2, C1010.2, C1011.2, C1012.2, C1013.2, C1014.2, C1015.2, C1016.2, C1017.2, C1018.2, C1019.2, C1020.2, C1021.2, C1022.2, C1023.2, C1024.2, C1025.2, C1026.2, C1027.2, C1028.1, C1029.1, C1030.1, C1031.2, C1032.2, C1033.2, C1034.2, C1035.2, C1036.2, C1037.2, C1038.2, C1039.2, C1040.2, C1041.2, C1042.2, C1043.2, C1044.2, C1045.2, C1046.2, C1047.2, C1048.2, C1049.2, C1050.2, C1051.2, C1052.2, C1053.2, C1054.2, C1055.2, C1056.2, C1057.2, C1058.2, J1001.2, J1001.4, J1001.6, J1001.8, J1001.10, J1001.12, J1002.A1 (GND), J1002.A12 (GND), J1002.B1 (GND), J1002.B12 (GND), Q1001.2 (S), R1016.2, R1017.2, R1020.2, R1021.2, R1029.2, R1033.2, SW1001.1, SW1001.3 (Shield), U1001.4 (GND), U1002.1 (GND), U1002.5 (GND), U1002.9 (GND), U1002.37 (GND), U1002.44 (GND), U1002.50 (GND), U1002.64 (GND), U1002.94 (GND), U1002.104 (GND), U1002.108 (GND), U1002.120 (GND), U1002.121 (GND), U1002.126 (GND), U1002.127 (GND), U1002.129 (GND), U1002.133 (GND), U1003.25 (GND), U1004.6 (VSSQ), U1004.12 (VSSQ), U1004.28 (VSS), U1004.41 (VSS), U1004.46 (VSSQ), U1004.52 (VSSQ), U1004.54 (VSS), U1005.2 (GND), U1006.2 (GND), X1001.2 (GND), Y1001.2, Y1001.4
unnamed: C1043.1, C1044.1, C1045.1, C1046.1, C1047.1, L1004.1, U1004.3 (VDDQ), U1004.9 (VDDQ), U1004.43 (VDDQ), U1004.49 (VDDQ)
unnamed: C1055.1, C1056.1, L1005.1, R1027.1, R1028.2
unnamed: C1058.1, L1006.1, R1031.1, R1032.2
unnamed: D1001.1 (K1), R1012.2
unnamed: D1001.3 (K2), R1013.1
unnamed: J1001.1, R1001.2, U1001.1 (~CS), U1002.31 (GPIOL_00_SS_N)
unnamed: C1003.1, J1001.3, R1008.2, SW1001.2, U1002.35 (CRESET_N)
unnamed: J1001.5, R1005.2, U1002.27 (TDI)
unnamed: J1001.7, R1006.2, U1002.24 (TDO)
unnamed: J1001.9, R1004.2, U1002.26 (TCK)
unnamed: J1001.11, R1007.2, U1002.25 (TMS)
unnamed: J1001.13, R1003.2
unnamed: J1002.A5 (CC1), R1017.1
unnamed: J1002.B5 (CC2), R1016.1
unnamed: C1032.1, J1002.S1 (SHIELD), R1020.1
unnamed: Q1001.3 (D), R1013.2
unnamed: Q1001.1 (G), R1009.2, R1012.1, U1002.34 (CDONE)
unnamed: U1001.6 (SCK), U1002.30 (GPIOL_01_CCK)
unnamed: U1001.5 (SI/IO0), U1002.29 (GPIOL_08_CDI0)
unnamed: U1001.2 (SO/IO1), U1002.28 (GPIOL_09_CDI1)
unnamed: R1010.2, U1001.7 (~HOLD/IO3)
unnamed: R1011.2, U1001.3 (~WP/IO2)
unnamed: R1002.2, U1002.32 (GPIOL_04_CSI)
unnamed: U1002.75 (GPIOR_157_PLLIN), X1001.3 (OUT)
unnamed: C1008.1, C1009.1, L1001.2, U1002.73 (VCCA_BR)
unnamed: C1010.1, C1011.1, L1002.2, U1002.2 (VCCA_TL)
unnamed: C1012.1, C1013.1, L1003.2, U1002.107 (VCCA_TR)
unnamed: C1028.2, U1003.15 (VDD33), U1003.18 (ID)
unnamed: R1021.1, U1003.19 (RBIAS)
unnamed: C1034.1, R1019.2, U1003.21 (REFCLK/XI), Y1001.3
unnamed: R1018.2, U1003.17 (VBUS)
unnamed: C1029.2, U1003.23 (VDD18)
unnamed: C1033.1, R1019.1, U1003.20 (XO), Y1001.1
unnamed: R1014.2, R1015.2, U1003.22 (~RESETB)
unnamed: R1028.1, R1029.1, U1005.6 (FB)
unnamed: R1030.2, U1005.5 (PG), U1006.1 (EN)
unnamed: L1005.2, U1005.3 (SW)
unnamed: R1032.1, R1033.1, U1006.6 (FB)
unnamed: L1006.2, U1006.3 (SW)
SDRAM_A4: U1002.110 (GPIOR_87_CDI29), U1004.29 (A4)
SDRAM_A5: U1002.109 (GPIOR_88_CDI28), U1004.30 (A5)
SDRAM_A11: U1002.112 (GPIOR_86), U1004.35 (A11)
SDRAM_A12: U1002.111 (GPIOR_85), U1004.36 (A12)
SDRAM_CKE: U1002.113 (GPIOR_84), U1004.37 (CKE)
SDRAM_DQ0: U1002.33 (GPIOL_05_CSO), U1004.2 (DQ0)
ULPI_CLK: U1002.132 (GPIOL_74_PLLIN0), U1003.2 (CLKOUT)
ULPI_DIR: U1002.134 (GPIOL_73_EXTFB1_CDI15), U1003.1 (DIR)
ULPI_NXT: U1002.131 (GPIOL_75_PLLIN1), U1003.3 (NXT)
ULPI_RSTb: R1015.1, U1002.138 (GPIOL_69_CBSEL1)
ULPI_STP: U1002.135 (GPIOL_72_EXTFB0_CDI14), U1003.24 (STP)
